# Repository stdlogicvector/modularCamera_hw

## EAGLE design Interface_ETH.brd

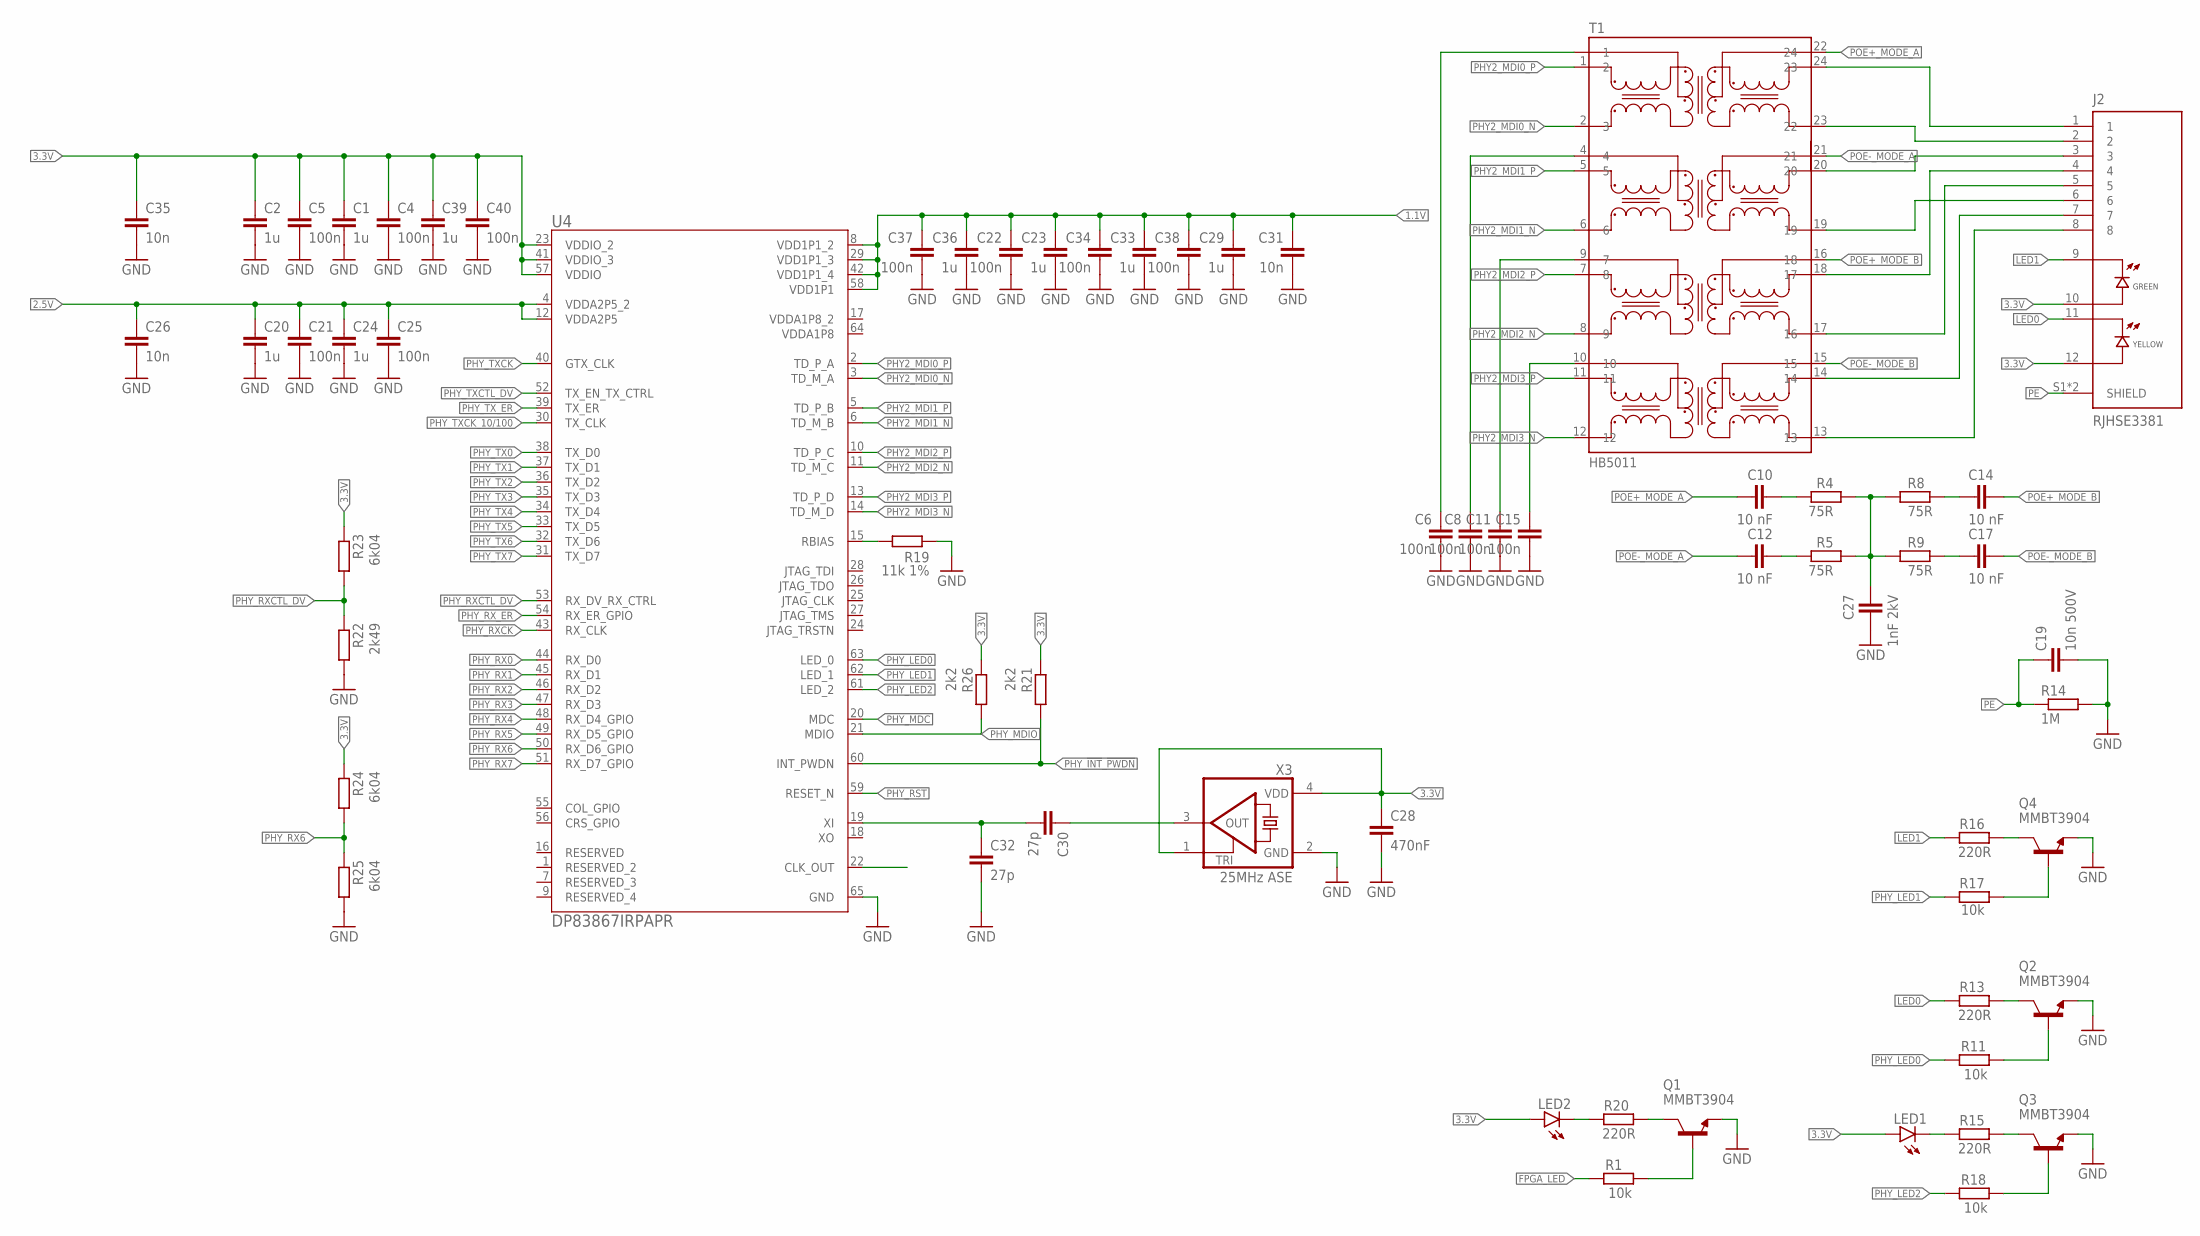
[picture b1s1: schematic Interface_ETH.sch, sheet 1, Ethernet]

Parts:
C1, C2, C20, C23, C24, C29, C33, C36, C39: 1u; C0402; FARNELL 2409032
C4, C5, C6, C8, C11, C15, C21, C22, C25, C34, C37, C38, C40: 100n; C0402; FARNELL 2409032
C10, C12, C14, C17: 10 nF; C0603; FARNELL 1288254
C19: 10n 500V; C0805
C26, C31, C35: 10n; C0402; FARNELL 2409032
C27: 1nF 2kV; C1206; FARNELL 1650716
C28: 470nF; C0402; FARNELL 2409032
C30, C32: 27p; C0402; FARNELL 2409032
J2: RJHSE3381; AMPHENOL_RJHSE3381; DIGIKEY 664-RJHSE3381-ND
LED1: LEDCHIP-LED0805; CHIP-LED0805
LED2: LEDCHIP-LED0603; CHIP-LED0603
Q1, Q2, Q3, Q4: MMBT3904; SOT23; FARNELL 1757935
R1, R11, R17, R18: 10k; R0603
R4, R5, R8, R9: 75R; R0603; FARNELL 1527343
R13, R15, R16, R20: 220R; R0603
R14: 1M; R0603
R19: 11k 1%; R0402; FARNELL 1652885
R21, R26: 2k2; R0402; FARNELL 1652885
R22: 2k49; R0402; FARNELL 1652885
R23, R24, R25: 6k04; R0402; FARNELL 1652885
T1: HB5011; DIGIKEY 931-TM82467NLCT-ND
U4: DP83867IRPAPR; PAP0064M_N
X3: 25MHz ASE; ASE; DIGIKEY 535-9577-1-ND

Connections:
1.1V: C22.1, C23.1, C29.1, C31.1, C33.1, C34.1, C36.1, C37.1, C38.1, U4.8 (VDD1P1_2), U4.29 (VDD1P1_3), U4.42 (VDD1P1_4), U4.58 (VDD1P1); also elsewhere on the board
2.5V: C20.1, C21.1, C24.1, C25.1, C26.1, U4.4 (VDDA2P5_2), U4.12 (VDDA2P5); also elsewhere on the board
3.3V: C1.1, C2.1, C4.1, C5.1, C28.1, C35.1, C39.1, C40.1, J2.10, J2.12, LED1.A, LED2.A, R21.1, R23.1, R24.1, R26.1, U4.23 (VDDIO_2), U4.41 (VDDIO_3), U4.57 (VDDIO), X3.1 (TRI), X3.4 (VDD); also elsewhere on the board
ETH_1: J2.1, T1.24 (23)
ETH_2: J2.2, T1.23 (22)
ETH_3: J2.3, T1.20
ETH_4: J2.4, T1.18 (17)
ETH_5: J2.5, T1.17 (16)
ETH_6: J2.6, T1.19
ETH_7: J2.7, T1.14
ETH_8: J2.8, T1.13
FPGA_LED: R1.1; also elsewhere on the board
GND: C1.2, C2.2, C4.2, C5.2, C6.2, C8.2, C11.2, C15.2, C19.2, C20.2, C21.2, C22.2, C23.2, C24.2, C25.2, C26.2, C27.2, C28.2, C29.2, C31.2, C32.2, C33.2, C34.2, C35.2, C36.2, C37.2, C38.2, C39.2, C40.2, Q1.2 (E), Q2.2 (E), Q3.2 (E), Q4.2 (E), R14.2, R19.1, R22.2, R25.2, U4.65 (GND), X3.2 (GND); also elsewhere on the board
LED0: J2.11, R13.1
LED1: J2.9, R16.1
unnamed: C30.1, X3.3 (OUT)
unnamed: Q3.3 (C), R15.2
unnamed: Q3.1 (B), R18.2
unnamed: C15.1, T1.10
unnamed: C11.1, T1.9 (7)
unnamed: C8.1, T1.4
unnamed: C6.1, T1.3 (1)
unnamed: C30.2, C32.1, U4.19 (XI)
unnamed: Q1.3 (C), R20.2
unnamed: LED1.C, R15.1
unnamed: Q1.1 (B), R1.2
unnamed: LED2.C, R20.1
unnamed: C14.1, R8.2
unnamed: C17.1, R9.2
unnamed: C10.1, R4.2
unnamed: C12.1, R5.2
unnamed: C27.1, R4.1, R5.1, R8.1, R9.1
unnamed: R19.2, U4.15 (RBIAS)
unnamed: Q4.3 (C), R16.2
unnamed: Q2.3 (C), R13.2
unnamed: Q4.1 (B), R17.2
unnamed: Q2.1 (B), R11.2
PE: C19.1, J2.S1 (SHIELD), J2.S2 (SHIELD), R14.1; also elsewhere on the board
PHY2_MDI0_N: T1.2 (3), U4.3 (TD_M_A)
PHY2_MDI0_P: T1.1 (2), U4.2 (TD_P_A)
PHY2_MDI1_N: T1.6, U4.6 (TD_M_B)
PHY2_MDI1_P: T1.5, U4.5 (TD_P_B)
PHY2_MDI2_N: T1.8 (9), U4.11 (TD_M_C)
PHY2_MDI2_P: T1.7 (8), U4.10 (TD_P_C)
PHY2_MDI3_N: T1.12, U4.14 (TD_M_D)
PHY2_MDI3_P: T1.11, U4.13 (TD_P_D)
PHY_!INT!_!PWDN: R21.2, U4.60 (INT_PWDN); also elsewhere on the board
PHY_LED0: R11.1, U4.63 (LED_0)
PHY_LED1: R17.1, U4.62 (LED_1)
PHY_LED2: R18.1, U4.61 (LED_2)
PHY_MDC: U4.20 (MDC); also elsewhere on the board
PHY_MDIO: R26.2, U4.21 (MDIO); also elsewhere on the board
PHY_RST: U4.59 (RESET_N); also elsewhere on the board
PHY_RX0: U4.44 (RX_D0); also elsewhere on the board
PHY_RX1: U4.45 (RX_D1); also elsewhere on the board
PHY_RX2: U4.46 (RX_D2); also elsewhere on the board
PHY_RX3: U4.47 (RX_D3); also elsewhere on the board
PHY_RX4: U4.48 (RX_D4_GPIO); also elsewhere on the board
PHY_RX5: U4.49 (RX_D5_GPIO); also elsewhere on the board
PHY_RX6: R24.2, R25.1, U4.50 (RX_D6_GPIO); also elsewhere on the board
PHY_RX7: U4.51 (RX_D7_GPIO); also elsewhere on the board
PHY_RXCK: U4.43 (RX_CLK); also elsewhere on the board
PHY_RXCTL_DV: R22.1, R23.2, U4.53 (RX_DV_RX_CTRL); also elsewhere on the board
PHY_RX_ER: U4.54 (RX_ER_GPIO); also elsewhere on the board
PHY_TX0: U4.38 (TX_D0); also elsewhere on the board
PHY_TX1: U4.37 (TX_D1); also elsewhere on the board
PHY_TX2: U4.36 (TX_D2); also elsewhere on the board
PHY_TX3: U4.35 (TX_D3); also elsewhere on the board
PHY_TX4: U4.34 (TX_D4); also elsewhere on the board
PHY_TX5: U4.33 (TX_D5); also elsewhere on the board
PHY_TX6: U4.32 (TX_D6); also elsewhere on the board
PHY_TX7: U4.31 (TX_D7); also elsewhere on the board
PHY_TXCK: U4.40 (GTX_CLK); also elsewhere on the board
PHY_TXCK_10/100: U4.30 (TX_CLK); also elsewhere on the board
PHY_TXCTL_DV: U4.52 (TX_EN_TX_CTRL); also elsewhere on the board
PHY_TX_ER: U4.39 (TX_ER); also elsewhere on the board
POE+_MODE_A: C10.2, T1.22 (24); also elsewhere on the board
POE+_MODE_B: C14.2, T1.16 (18); also elsewhere on the board
POE-_MODE_A: C12.2, T1.21; also elsewhere on the board
POE-_MODE_B: C17.2, T1.15; also elsewhere on the board
VDDA1P8: U4.64 (VDDA1P8)
VDDA1P8_2: U4.17 (VDDA1P8_2)

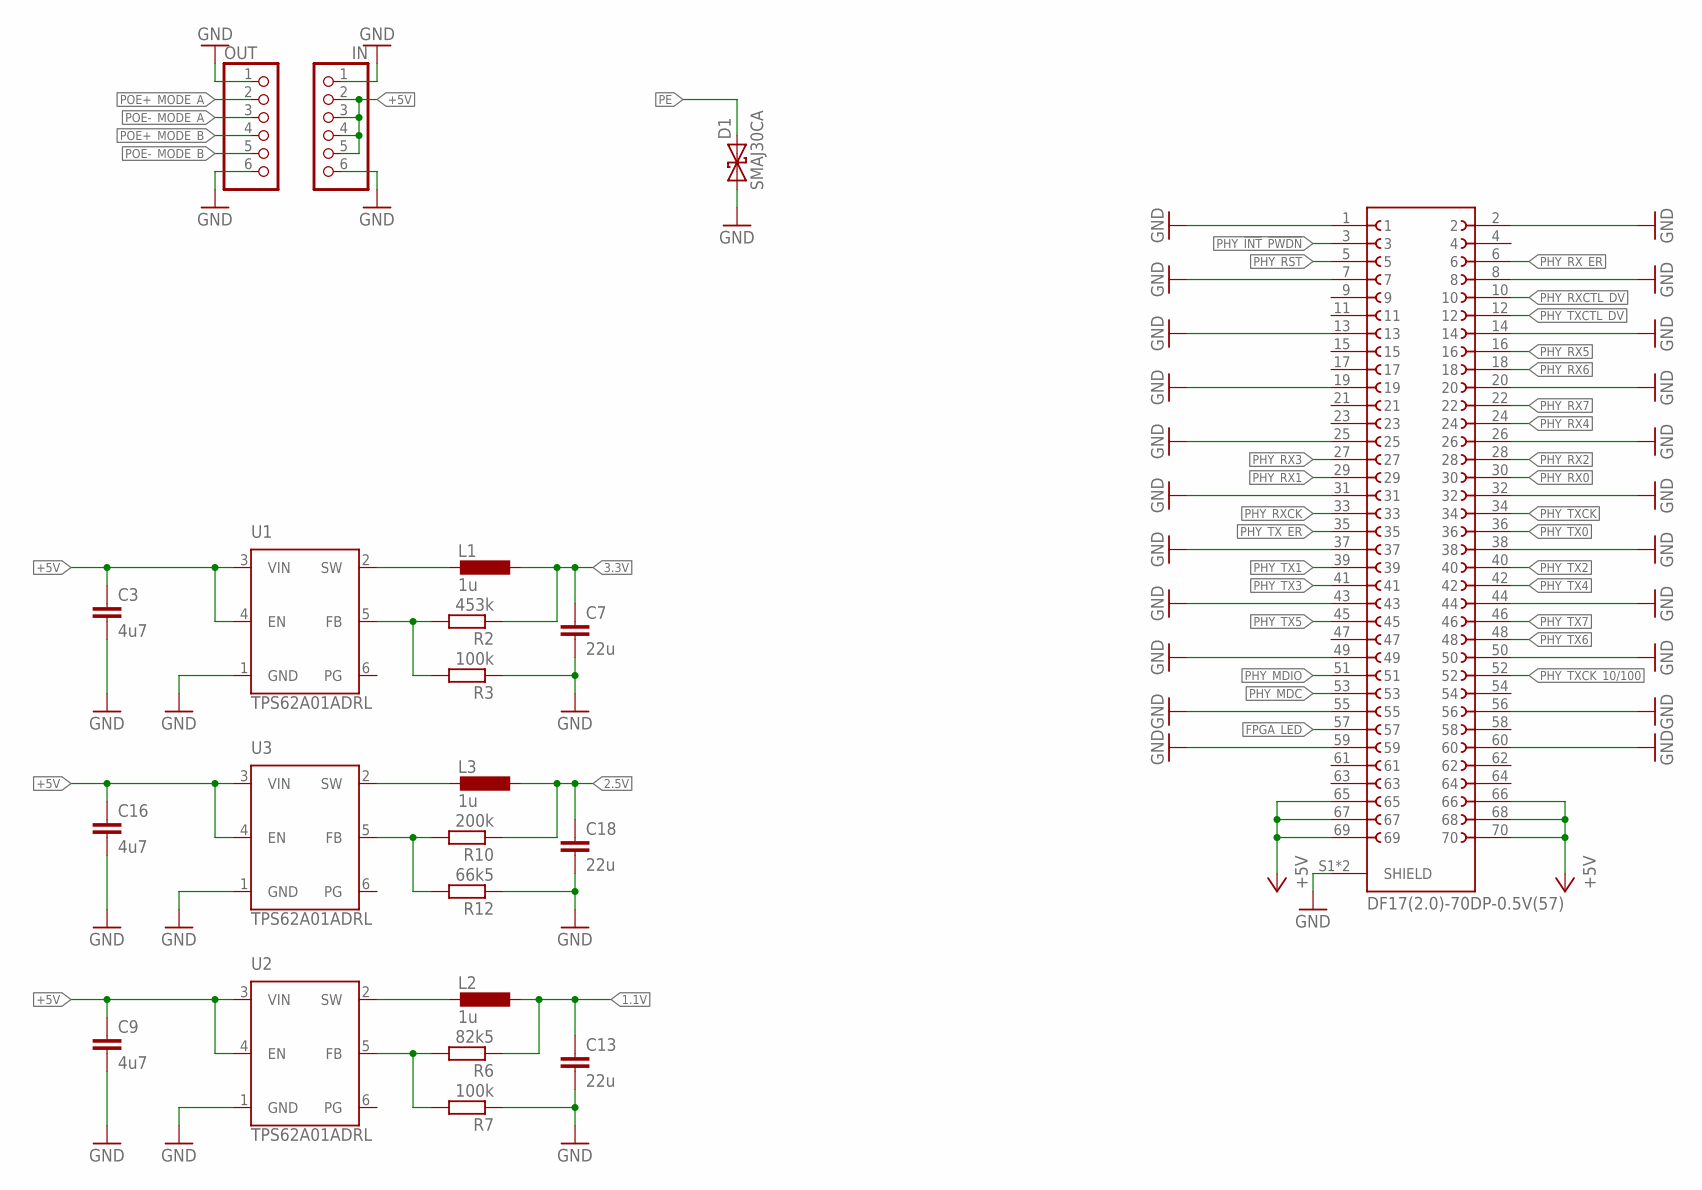
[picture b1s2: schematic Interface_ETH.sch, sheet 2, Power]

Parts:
C3, C9, C16: 4u7; C0603; LCSC C19666
C7, C13, C18: 22u; C0603; LCSC C109448
D1: SMAJ30CA; DO214AC; FARNELL 1827672
IN: PINHD-1X06_2.00; 1X06M
J1: DF17(2.0)-70DP-0.5V(57)
L1, L2, L3: 1u; L1008; MPN LQM2HPN1R0MG0L; DIGIKEY 490-5112-1-ND
OUT: PINHD-1X06_2.00; 1X06M
R2: 453k; R0402; LCSC C137978
R3: 100k; R0402; DIGIKEY RMCF0402FT100KCT-ND
R6: 82k5; R0402; DIGIKEY RMCF0402FT66K5CT-ND
R7: 100k; R0402; LCSC C60491
R10: 200k; R0402; LCSC C137978
R12: 66k5; R0402; DIGIKEY RMCF0402FT100KCT-ND
U1, U2, U3: TPS62A01ADRL; SOTFL50P160X60-6N; DIGIKEY 296-TPS62A01ADRLRCT-ND

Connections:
1.1V: C13.1, L2.1, R6.1; also elsewhere on the board
2.5V: C18.1, L3.1, R10.1; also elsewhere on the board
3.3V: C7.1, L1.1, R2.1; also elsewhere on the board
+5V: C3.1, C9.1, C16.1, IN.2, IN.3, IN.4, IN.5, J1.65, J1.66, J1.67, J1.68, J1.69, J1.70, U1.3 (VIN), U1.4 (EN), U2.3 (VIN), U2.4 (EN), U3.3 (VIN), U3.4 (EN)
FPGA_LED: J1.57; also elsewhere on the board
GND: C3.2, C7.2, C9.2, C13.2, C16.2, C18.2, D1.A (1), IN.1, IN.6, J1.1, J1.2, J1.7, J1.8, J1.13, J1.14, J1.19, J1.20, J1.25, J1.26, J1.31, J1.32, J1.37, J1.38, J1.43, J1.44, J1.49, J1.50, J1.55, J1.56, J1.59, J1.60, J1.S1 (SHIELD), J1.S2 (SHIELD), OUT.1, OUT.6, R3.1, R7.1, R12.1, U1.1 (GND), U2.1 (GND), U3.1 (GND); also elsewhere on the board
unnamed: L2.2, U2.2 (SW)
unnamed: L1.2, U1.2 (SW)
unnamed: L3.2, U3.2 (SW)
unnamed: R10.2, R12.2, U3.5 (FB)
unnamed: R6.2, R7.2, U2.5 (FB)
unnamed: R2.2, R3.2, U1.5 (FB)
PE: D1.C (2); also elsewhere on the board
PHY_!INT!_!PWDN: J1.3; also elsewhere on the board
PHY_MDC: J1.53; also elsewhere on the board
PHY_MDIO: J1.51; also elsewhere on the board
PHY_RST: J1.5; also elsewhere on the board
PHY_RX0: J1.30; also elsewhere on the board
PHY_RX1: J1.29; also elsewhere on the board
PHY_RX2: J1.28; also elsewhere on the board
PHY_RX3: J1.27; also elsewhere on the board
PHY_RX4: J1.24; also elsewhere on the board
PHY_RX5: J1.16; also elsewhere on the board
PHY_RX6: J1.18; also elsewhere on the board
PHY_RX7: J1.22; also elsewhere on the board
PHY_RXCK: J1.33; also elsewhere on the board
PHY_RXCTL_DV: J1.10; also elsewhere on the board
PHY_RX_ER: J1.6; also elsewhere on the board
PHY_TX0: J1.36; also elsewhere on the board
PHY_TX1: J1.39; also elsewhere on the board
PHY_TX2: J1.40; also elsewhere on the board
PHY_TX3: J1.41; also elsewhere on the board
PHY_TX4: J1.42; also elsewhere on the board
PHY_TX5: J1.45; also elsewhere on the board
PHY_TX6: J1.48; also elsewhere on the board
PHY_TX7: J1.46; also elsewhere on the board
PHY_TXCK: J1.34; also elsewhere on the board
PHY_TXCK_10/100: J1.52; also elsewhere on the board
PHY_TXCTL_DV: J1.12; also elsewhere on the board
PHY_TX_ER: J1.35; also elsewhere on the board
POE+_MODE_A: OUT.2; also elsewhere on the board
POE+_MODE_B: OUT.4; also elsewhere on the board
POE-_MODE_A: OUT.3; also elsewhere on the board
POE-_MODE_B: OUT.5; also elsewhere on the board

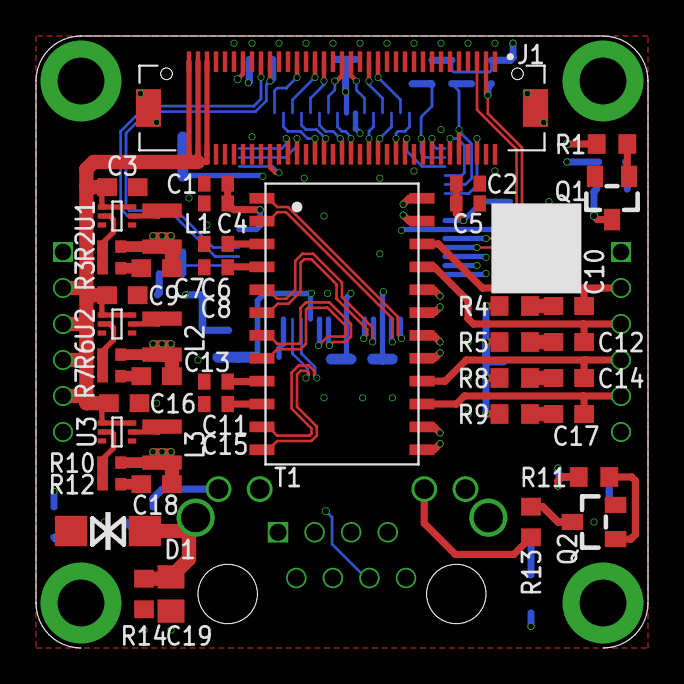
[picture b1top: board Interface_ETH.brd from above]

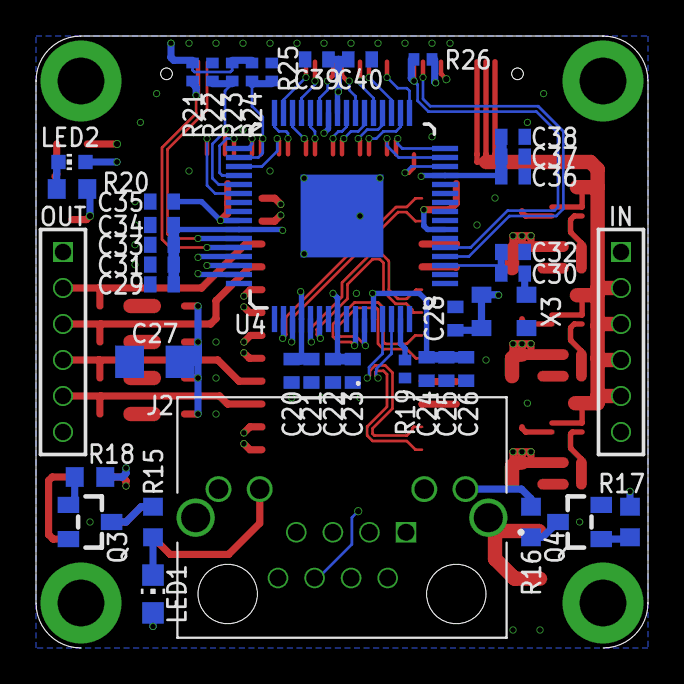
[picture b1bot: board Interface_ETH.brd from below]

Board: 4 copper layers, 34.0 x 34.0 mm, 86 parts (42 on the bottom side), 87 nets.

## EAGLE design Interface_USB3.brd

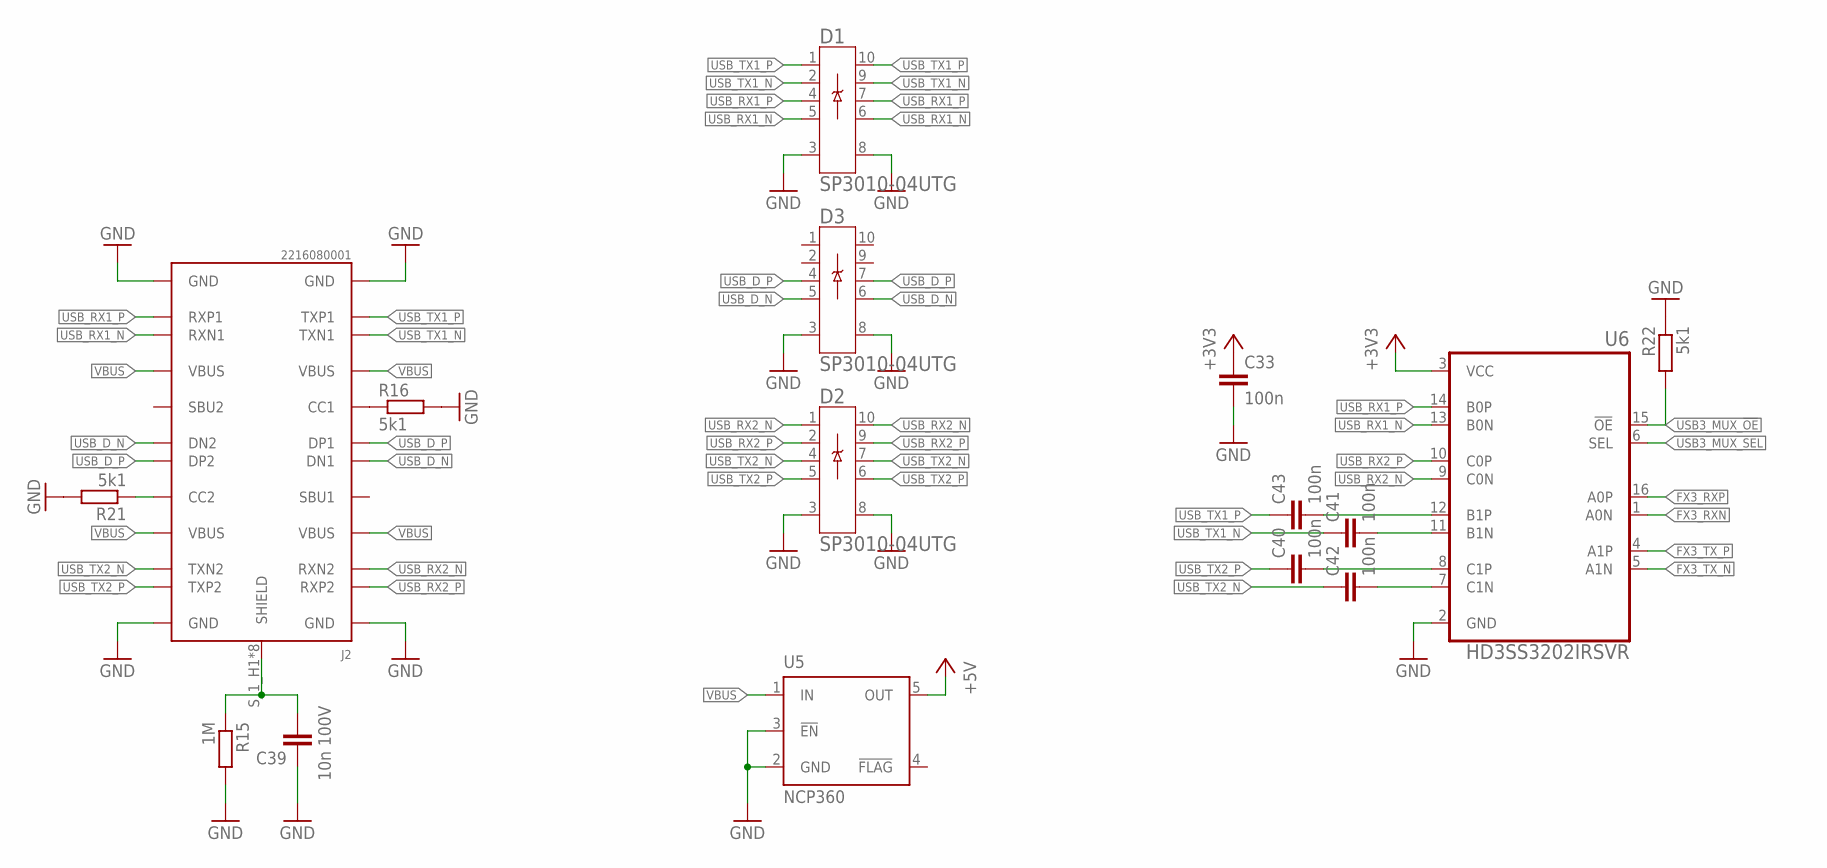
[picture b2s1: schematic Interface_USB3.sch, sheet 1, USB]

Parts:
C33, C40, C41, C42, C43: 100n; C0402; LCSC C1525
C39: 10n 100V; C0603; LCSC C84709
D1, D2, D3: SP3010-04UTG; UDFEN-10_MO229_LTF; LCSC C126837
J2: 2216080001; CONN_221608-0001_MOL; DIGIKEY 900-2216080001CT-ND
R15: 1M; R0603; LCSC C22935
R16, R21, R22: 5k1; R0402; LCSC C105872
U5: NCP360; TSOP-5; DIGIKEY NCP360SNT1GOSCT-ND
U6: HD3SS3202IRSVR; QFN40P180X260X55-16N_HD3SS3202IRSVR; LCSC C2150836

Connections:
+3V3: C33.1, U6.3 (VCC); also elsewhere on the board
+5V: U5.5 (OUT); also elsewhere on the board
CC1: J2.A5 (CC1), R16.1
CC2: J2.B5 (CC2), R21.1
FX3_RXN: U6.1 (A0N); also elsewhere on the board
FX3_RXP: U6.16 (A0P); also elsewhere on the board
FX3_TX_N: U6.5 (A1N); also elsewhere on the board
FX3_TX_P: U6.4 (A1P); also elsewhere on the board
GND: C33.2, C39.1, D1.3, D1.8, D2.3, D2.8, D3.3, D3.8, J2.A1 (GND), J2.A12 (GND), J2.B1 (GND), J2.B12 (GND), R15.2, R16.2, R21.2, R22.1, U5.2 (GND), U5.3 (!EN), U6.2 (GND); also elsewhere on the board
unnamed: C39.2, J2.S_1_H1 (SHIELD), J2.S_1_H2 (SHIELD), J2.S_2_H1 (SHIELD), J2.S_2_H2 (SHIELD), J2.S_3_H1 (SHIELD), J2.S_3_H2 (SHIELD), J2.S_4_H1 (SHIELD), J2.S_4_H2 (SHIELD), R15.1
unnamed: C42.2, U6.7 (C1N)
unnamed: C40.2, U6.8 (C1P)
unnamed: C41.2, U6.11 (B1N)
unnamed: C43.2, U6.12 (B1P)
USB3_MUX_!OE: R22.2, U6.15 (!OE); also elsewhere on the board
USB3_MUX_SEL: U6.6 (SEL); also elsewhere on the board
USB_D_N: D3.5, D3.6, J2.A7 (DN1), J2.B7 (DN2); also elsewhere on the board
USB_D_P: D3.4, D3.7, J2.A6 (DP1), J2.B6 (DP2); also elsewhere on the board
USB_RX1_N: D1.5, D1.6, J2.B10 (RXN1), U6.13 (B0N)
USB_RX1_P: D1.4, D1.7, J2.B11 (RXP1), U6.14 (B0P)
USB_RX2_N: D2.1, D2.10, J2.A10 (RXN2), U6.9 (C0N)
USB_RX2_P: D2.2, D2.9, J2.A11 (RXP2), U6.10 (C0P)
USB_TX1_N: C41.1, D1.2, D1.9, J2.A3 (TXN1)
USB_TX1_P: C43.1, D1.1, D1.10, J2.A2 (TXP1)
USB_TX2_N: C42.1, D2.4, D2.7, J2.B3 (TXN2)
USB_TX2_P: C40.1, D2.5, D2.6, J2.B2 (TXP2)
VBUS: J2.A4 (VBUS), J2.A9 (VBUS), J2.B4 (VBUS), J2.B9 (VBUS), U5.1 (IN)

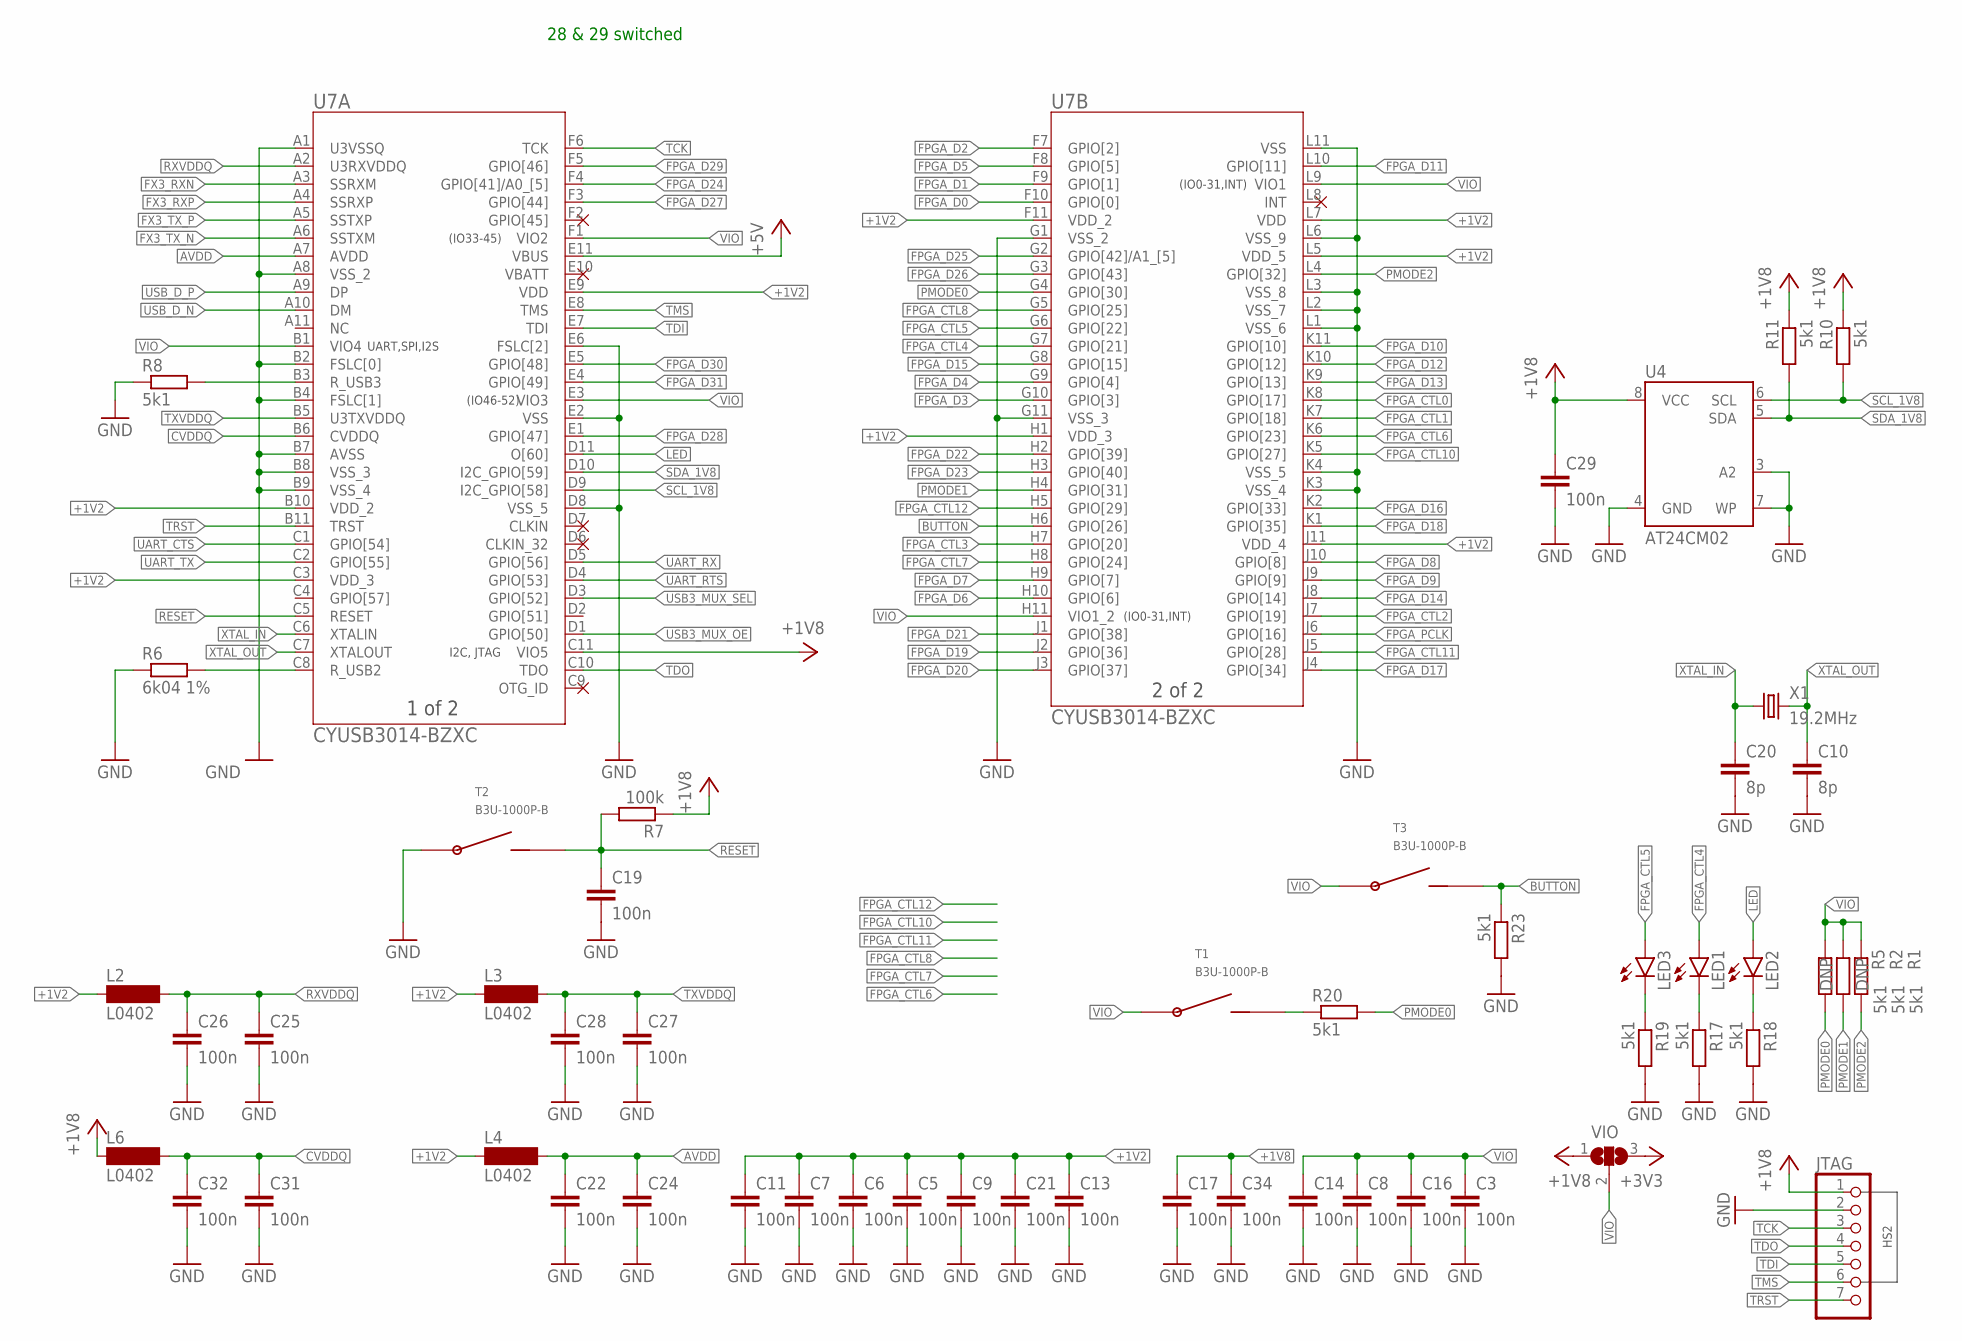
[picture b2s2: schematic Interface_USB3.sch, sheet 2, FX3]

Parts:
C3, C5, C6, C7, C8, C9, C11, C13, C14, C16, C17, C19, C21, C22, C24, C25, C26, C27, C28, C29, C31, C32, C34: 100n; C0402; LCSC C1525
C10, C20: 8p; C0402; LCSC C281765
JTAG: PINHD-1X7_2.00; 1X07M
L2, L3, L4, L6: L0402; C0402; LCSC C88970
LED1, LED2, LED3: LEDCHIPLED_0603; CHIPLED_0603; LCSC C7493803
R1, R2, R5, R8, R10, R11, R17, R18, R19, R20, R23: 5k1; R0402; LCSC C105872
R6: 6k04 1%; R0402; LCSC C97819
R7: 100k; R0402; DIGIKEY RMCF0402FT100KCT-ND
T1, T2, T3: B3U-1000P-B; FARNELL 1333654
U4: AT24CM02; SOIC8; DIGIKEY AT24CM02-SSHD-B-ND
U7: CYUSB3014-BZXC; PG-TFBGA-121-800_INF; LCSC C462526
VIO: SJ2W; SJ_2
X1: 19.2MHz; 2520; DIGIKEY XC3048CT-ND

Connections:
+1V2: C5.1, C6.1, C7.1, C9.1, C11.1, C13.1, C21.1, L2.1, L3.1, L4.1, U7.B10 (VDD_2), U7.C3 (VDD_3), U7.E9 (VDD), U7.F11 (VDD_2), U7.H1 (VDD_3), U7.J11 (VDD_4), U7.L5 (VDD_5), U7.L7 (VDD); also elsewhere on the board
+1V8: C17.1, C29.1, C34.1, JTAG.1, L6.1, R7.1, R10.1, R11.1, U4.8 (VCC), U7.C11 (VIO5), VIO.1; also elsewhere on the board
+3V3: VIO.3; also elsewhere on the board
+5V: U7.E11 (VBUS); also elsewhere on the board
AVDD: C22.1, C24.1, L4.2, U7.A7 (AVDD)
BUTTON: R23.1, T3.P$2, U7.H6 (GPIO[26])
CVDDQ: C31.1, C32.1, L6.2, U7.B6 (CVDDQ)
FPGA_CTL0: U7.K8 (GPIO[17]); also elsewhere on the board
FPGA_CTL1: U7.K7 (GPIO[18]); also elsewhere on the board
FPGA_CTL2: U7.J7 (GPIO[19]); also elsewhere on the board
FPGA_CTL3: U7.H7 (GPIO[20]); also elsewhere on the board
FPGA_CTL4: LED1.A, U7.G7 (GPIO[21])
FPGA_CTL5: LED3.A, U7.G6 (GPIO[22])
FPGA_CTL6: U7.K6 (GPIO[23])
FPGA_CTL7: U7.H8 (GPIO[24])
FPGA_CTL8: U7.G5 (GPIO[25])
FPGA_CTL10: U7.K5 (GPIO[27])
FPGA_CTL11: U7.J5 (GPIO[28])
FPGA_CTL12: U7.H5 (GPIO[29])
FPGA_D0: U7.F10 (GPIO[0]); also elsewhere on the board
FPGA_D1: U7.F9 (GPIO[1]); also elsewhere on the board
FPGA_D2: U7.F7 (GPIO[2]); also elsewhere on the board
FPGA_D3: U7.G10 (GPIO[3]); also elsewhere on the board
FPGA_D4: U7.G9 (GPIO[4]); also elsewhere on the board
FPGA_D5: U7.F8 (GPIO[5]); also elsewhere on the board
FPGA_D6: U7.H10 (GPIO[6]); also elsewhere on the board
FPGA_D7: U7.H9 (GPIO[7]); also elsewhere on the board
FPGA_D8: U7.J10 (GPIO[8]); also elsewhere on the board
FPGA_D9: U7.J9 (GPIO[9]); also elsewhere on the board
FPGA_D10: U7.K11 (GPIO[10]); also elsewhere on the board
FPGA_D11: U7.L10 (GPIO[11]); also elsewhere on the board
FPGA_D12: U7.K10 (GPIO[12]); also elsewhere on the board
FPGA_D13: U7.K9 (GPIO[13]); also elsewhere on the board
FPGA_D14: U7.J8 (GPIO[14]); also elsewhere on the board
FPGA_D15: U7.G8 (GPIO[15]); also elsewhere on the board
FPGA_D16: U7.K2 (GPIO[33]); also elsewhere on the board
FPGA_D17: U7.J4 (GPIO[34]); also elsewhere on the board
FPGA_D18: U7.K1 (GPIO[35]); also elsewhere on the board
FPGA_D19: U7.J2 (GPIO[36]); also elsewhere on the board
FPGA_D20: U7.J3 (GPIO[37]); also elsewhere on the board
FPGA_D21: U7.J1 (GPIO[38]); also elsewhere on the board
FPGA_D22: U7.H2 (GPIO[39]); also elsewhere on the board
FPGA_D23: U7.H3 (GPIO[40]); also elsewhere on the board
FPGA_D24: U7.F4 (GPIO[41]/A0_[5]); also elsewhere on the board
FPGA_D25: U7.G2 (GPIO[42]/A1_[5]); also elsewhere on the board
FPGA_D26: U7.G3 (GPIO[43]); also elsewhere on the board
FPGA_D27: U7.F3 (GPIO[44]); also elsewhere on the board
FPGA_D28: U7.E1 (GPIO[47]); also elsewhere on the board
FPGA_D29: U7.F5 (GPIO[46]); also elsewhere on the board
FPGA_D30: U7.E5 (GPIO[48]); also elsewhere on the board
FPGA_D31: U7.E4 (GPIO[49]); also elsewhere on the board
FPGA_PCLK: U7.J6 (GPIO[16]); also elsewhere on the board
FX3_RXN: U7.A3 (SSRXM); also elsewhere on the board
FX3_RXP: U7.A4 (SSRXP); also elsewhere on the board
FX3_TX_N: U7.A6 (SSTXM); also elsewhere on the board
FX3_TX_P: U7.A5 (SSTXP); also elsewhere on the board
GND: C3.2, C5.2, C6.2, C7.2, C8.2, C9.2, C10.2, C11.2, C13.2, C14.2, C16.2, C17.2, C19.2, C20.2, C21.2, C22.2, C24.2, C25.2, C26.2, C27.2, C28.2, C29.2, C31.2, C32.2, C34.2, JTAG.2, R6.1, R8.1, R17.2, R18.2, R19.2, R23.2, T2.P$1, U4.3 (A2), U4.4 (GND), U4.7 (WP), U7.A1 (U3VSSQ), U7.A8 (VSS_2), U7.B2 (FSLC[0]), U7.B4 (FSLC[1]), U7.B7 (AVSS), U7.B8 (VSS_3), U7.B9 (VSS_4), U7.D8 (VSS_5), U7.E2 (VSS), U7.E6 (FSLC[2]), U7.G1 (VSS_2), U7.G11 (VSS_3), U7.K3 (VSS_4), U7.K4 (VSS_5), U7.L1 (VSS_6), U7.L2 (VSS_7), U7.L3 (VSS_8), U7.L6 (VSS_9), U7.L11 (VSS); also elsewhere on the board
LED: LED2.A, U7.D11 (O[60])
unnamed: LED2.C, R18.1
unnamed: R6.2, U7.C8 (R_USB2)
unnamed: R8.2, U7.B3 (R_USB3)
unnamed: LED1.C, R17.1
unnamed: LED3.C, R19.1
unnamed: R20.1, T1.P$2
PMODE0: R5.2, R20.2, U7.G4 (GPIO[30])
PMODE1: R2.2, U7.H4 (GPIO[31])
PMODE2: R1.2, U7.L4 (GPIO[32])
RESET: C19.1, R7.2, T2.P$2, U7.C5 (RESET)
RXVDDQ: C25.1, C26.1, L2.2, U7.A2 (U3RXVDDQ)
SCL_1V8: R10.2, U4.6 (SCL), U7.D9 (I2C_GPIO[58])
SDA_1V8: R11.2, U4.5 (SDA), U7.D10 (I2C_GPIO[59])
TCK: JTAG.3, U7.F6 (TCK)
TDI: JTAG.5, U7.E7 (TDI)
TDO: JTAG.4, U7.C10 (TDO)
TMS: JTAG.6, U7.E8 (TMS)
TRST: JTAG.7, U7.B11 (TRST)
TXVDDQ: C27.1, C28.1, L3.2, U7.B5 (U3TXVDDQ)
UART_CTS: U7.C1 (GPIO[54]); also elsewhere on the board
UART_RTS: U7.D4 (GPIO[53]); also elsewhere on the board
UART_RX: U7.D5 (GPIO[56]); also elsewhere on the board
UART_TX: U7.C2 (GPIO[55]); also elsewhere on the board
USB3_MUX_!OE: U7.D1 (GPIO[50]); also elsewhere on the board
USB3_MUX_SEL: U7.D3 (GPIO[52]); also elsewhere on the board
USB_D_N: U7.A10 (DM); also elsewhere on the board
USB_D_P: U7.A9 (DP); also elsewhere on the board
VBATT: U7.E10 (VBATT)
VIO: C3.1, C8.1, C14.1, C16.1, R1.1, R2.1, R5.1, T1.P$1, T3.P$1, U7.B1 (VIO4), U7.E3 (VIO3), U7.F1 (VIO2), U7.H11 (VIO1_2), U7.L9 (VIO1), VIO.2
XTAL_IN: C20.1, U7.C6 (XTALIN), X1.1
XTAL_OUT: C10.1, U7.C7 (XTALOUT), X1.3 (2)

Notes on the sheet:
HS2
I2C, JTAG
UART,SPI,I2S
(IO33-45)
(IO46-52)
(IO0-31,INT)
28 & 29 switched

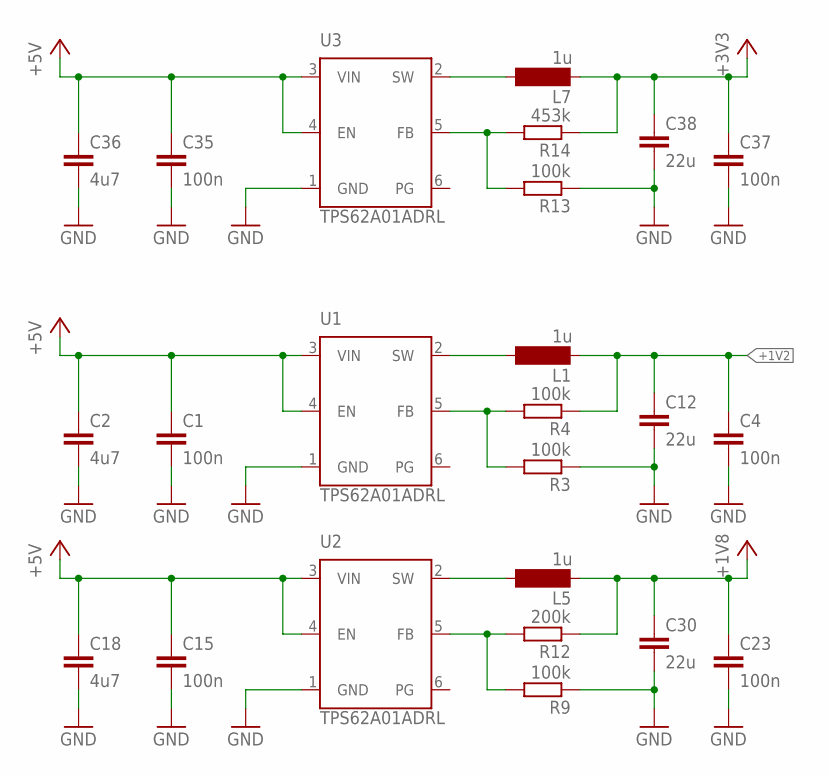
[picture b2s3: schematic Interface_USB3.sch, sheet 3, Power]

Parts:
C1, C4, C15, C23, C35, C37: 100n; C0402; LCSC C1525
C2, C18, C36: 4u7; C0603; LCSC C19666
C12, C30, C38: 22u; C0603; LCSC C723633
L1, L5, L7: 1u; L1008; MPN LQM2HPN1R0MG0L; DIGIKEY 490-5112-1-ND
R3, R4, R9, R13: 100k; R0402; DIGIKEY RMCF0402FT100KCT-ND
R12: 200k; R0402; DIGIKEY 311-200KLRCT-ND
R14: 453k; R0402; LCSC C137978
U1, U2, U3: TPS62A01ADRL; SOTFL50P160X60-6N; DIGIKEY 296-TPS62A01ADRLRCT-ND

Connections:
+1V2: C4.1, C12.1, L1.1, R4.1; also elsewhere on the board
+1V8: C23.1, C30.1, L5.1, R12.1; also elsewhere on the board
+3V3: C37.1, C38.1, L7.1, R14.1; also elsewhere on the board
+5V: C1.1, C2.1, C15.1, C18.1, C35.1, C36.1, U1.3 (VIN), U1.4 (EN), U2.3 (VIN), U2.4 (EN), U3.3 (VIN), U3.4 (EN); also elsewhere on the board
GND: C1.2, C2.2, C4.2, C12.2, C15.2, C18.2, C23.2, C30.2, C35.2, C36.2, C37.2, C38.2, R3.1, R9.1, R13.1, U1.1 (GND), U2.1 (GND), U3.1 (GND); also elsewhere on the board
unnamed: L1.2, U1.2 (SW)
unnamed: L7.2, U3.2 (SW)
unnamed: R13.2, R14.2, U3.5 (FB)
unnamed: R3.2, R4.2, U1.5 (FB)
unnamed: L5.2, U2.2 (SW)
unnamed: R9.2, R12.2, U2.5 (FB)

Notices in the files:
parts and their libraries:
m-pad-2.1: License : GNU General Public License version 2 (see bottom)
cypress: COPYRIGHT: Copyright (C) 2025 Ultra Librarian. All rights reserved.
crystal-geyer_V1_0: Copyright: Geyer-Electronic
